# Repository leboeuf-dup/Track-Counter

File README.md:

# Track Counter

An automated, low-power Track Counter that detects and records visitor traffic on walking and mountain-bike trails, removing the need for manual counts. Built as a proof-of-concept for organizations such as the Department of Conservation (DOC), the device uses an infrared (IR) sensor to detect passing visitors, stores the count locally on an Arduino, outputs a trigger pulse for optional external devices (e.g. a camera), and displays the accumulated count on an LCD at the press of a button.

Created: March 2025\
GitHub upload: Jul 2026

## Contributors

- Liam du Plessis
- Mark Watkins
- Samuel Holmes

## Breadboard prototype & Schematics

## Design Overview

The Track Counter meets the following design requirements:

- Uses a Sharp IR distance sensor to detect visitors on the track
- Stores the detection count locally, with no external cable or internet connection required
- Outputs a rectangular "trigger" pulse (50–100 ms, 4.5–5.2 V) with each detection
- Displays the count on an LCD at the press of a button
- Allows the count to be reset at the press of a separate button
- Detects visitors within a range of 40 cm (adjustable in software)
- Runs from a 5 V DC, 10,000 mAh power supply

## Hardware Description

| Building Block | Description |
|---|---|
| Arduino UNO R3 | Executes the program, stores the detection count, and communicates with all other components |
| Sharp IR Sensor (GP2Y0A21YK) | Converts a measured distance into a corresponding voltage signal |
| Low-Pass Filter | Passive RC filter (1 µF capacitor, 1.59 kΩ resistor, ~100 Hz cutoff) that removes high-frequency noise from the sensor signal before it reaches the Arduino |
| LCD Display Module (16×2, I2C) | Displays the current count to the surveyor |
| Tact Switches | Two buttons — a larger one to activate the display, and a smaller, less accessible one to reset the count — each using a 10 kΩ pull-down resistor for a clearly defined signal |

**Schematic**

**Arduino pin mapping:**

| Pin | Signal Type | Linked Component |
|---|---|---|
| A0 | Analog Input | IR sensor (via low-pass filter) |
| A4 / SDA | Analog | LCD module |
| A5 / SCL | Analog | LCD module |
| D2 | Digital Input | Display switch |
| D3 | Digital Output | Trigger signal |
| D4 | Digital Input | Reset switch |

A low-pass filter (rather than a Schmitt trigger) was chosen to clean up the IR sensor signal, as it is a cheap, compact, passive solution that avoids the extra power draw of an op-amp. Schematics and prototype photos are included in the full project report.

**Low-Pass Filter**

\
Before VS After signal

## Software Description

The Arduino is programmed via the Arduino IDE and runs a simple state-driven main loop:

1. On startup, the program initializes a `count` variable (set to 0) and a `tickOver` locking variable (set to locked).
2. Each loop iteration, the IR sensor voltage is read and passed through a low-pass filter.
3. When the sensor voltage crosses below the `CROSS_OVER_VOLTAGE` threshold, an object is considered "detected" and the counter unlocks.
4. When the voltage crosses back above the threshold (object leaving range), the `count` is incremented once, a 5 V trigger pulse is output, and the counter re-locks — preventing a single visitor from being counted multiple times while in range.
5. On every loop iteration, the count is written to the LCD (regardless of lock state), and the display/reset buttons are checked so they remain responsive at all times.
6. Pressing the display button turns the LCD on; releasing it turns the LCD off (a pull-down resistor prevents floating-voltage flicker).
7. Pressing the reset button clears the LCD and sets `count` back to 0, without resetting the entire Arduino program.

The LCD is driven using [Bill Perry's hd44780 library](https://github.com/duinoWitchery/hd44780), communicating over I2C (SDA/SCL).

## Bill of Materials

Total hardware cost: **$22.84 NZD** (well within the $40 budget constraint)

| Component | Quantity | Unit Cost ($) | Total Cost ($) |
|---|---|---|---|
| LCD Module | 1 | 6.00 | 6.00 |
| IR Distance Sensor | 1 | 6.80 | 6.80 |
| Solid Core Wire (per metre) | 0.05 m | 0.70 | 0.04 |
| Dupont Cables (M–M) | 7 | 0.00 | 0.00 |
| Dupont Cables (M–F) | 4 | 0.00 | 0.00 |
| Momentary Tact Switch (6 mm) | 1 | 0.25 | 0.25 |
| Momentary Tact Switch (12 mm) | 1 | 0.65 | 0.65 |
| Electrolytic Capacitor (1 µF) | 1 | 0.10 | 0.10 |
| Resistor | 4 | 0.00 | 0.00 |
| Arduino UNO | 1 | 9.00 | 9.00 |
| **Total** | | | **22.84** |

*Component pricing based on the UC Components Store catalogue.*

## Known Limitations

- Battery life is estimated at **5.95 days** under continuous sensor operation with a 10,000 mAh supply — short of the 10-day target. Limiting sensor activity to daylight hours (~12 hrs/day) improves this to ~7.72 days; further options include a FET-controlled sensor power switch for scheduled sensing windows.
- Groups of visitors passing closely together may be counted as a single detection event, due to the locking mechanism used to prevent multi-counting.

## Early Version PCB

This project followed introdutory labs in which initial versions of the step counter was made. This version includes a PCB layout shown below.

\
PCB Layout (Made by Liam du Plessis)

\
PCB CAD Model

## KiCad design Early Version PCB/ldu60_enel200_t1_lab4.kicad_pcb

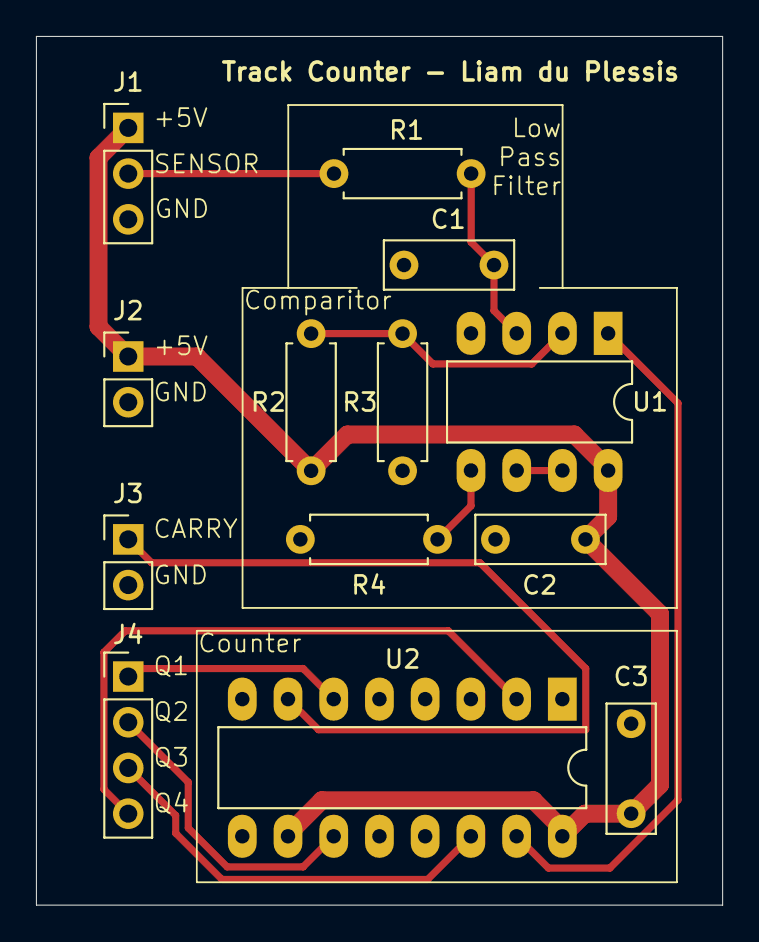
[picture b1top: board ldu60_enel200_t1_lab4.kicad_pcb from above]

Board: 2 copper layers, 38.1 x 48.3 mm, 13 parts (0 on the bottom side), 13 nets.

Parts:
C1: 1u; C_Rect_L7.0mm_W2.5mm_P5.00mm
C2, C3: 0.1u; C_Rect_L7.0mm_W2.5mm_P5.00mm
J1: UC_CONN_01X03; PinHeader_1x03_P2.54mm_Vertical
J2, J3: UC_CONN_01X02; PinHeader_1x02_P2.54mm_Vertical
J4: UC_CONN_01X04; PinHeader_1x04_P2.54mm_Vertical
R1: 1.59k; R_Axial_DIN0207_L6.3mm_D2.5mm_P7.62mm_Horizontal
R2: 567k; R_Axial_DIN0207_L6.3mm_D2.5mm_P7.62mm_Horizontal
R3, R4: 100k; R_Axial_DIN0207_L6.3mm_D2.5mm_P7.62mm_Horizontal
U1: UC_LM358; DIP-8_W7.62mm_LongPads
U2: UC_CD4510B; DIP-16_W7.62mm_LongPads

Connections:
+5V: C2.1, C3.1, J1.1, J2.1, R2.1, U1.8 (V+), U2.10 (U/D), U2.16 (VDD)
/SENSOR_VO: J1.2, R1.2
CARRY: J3.1, U2.7 (~COUT)
CLOCK: U1.1, U2.15 (CLK)
FILTERED: C1.1, R1.1, U1.3 (+)
GND: C1.2, C2.2, C3.2, J1.3, J2.2, J3.2, R3.1, R4.1, U1.4 (V-), U2.1 (PEN), U2.5 (~CIN), U2.8 (VSS), U2.9 (RST)
unnamed: R2.2, R3.2, U1.2 (-)
unnamed: R4.2, U1.5 (+)
unnamed: U1.6 (-), U1.7
Q1: J4.1, U2.6 (Q1)
Q2: J4.2, U2.11 (Q2)
Q3: J4.3, U2.14 (Q3)
Q4: J4.4, U2.2 (Q4)
